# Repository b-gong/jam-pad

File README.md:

# jam-pad
Just Another Macro Pad

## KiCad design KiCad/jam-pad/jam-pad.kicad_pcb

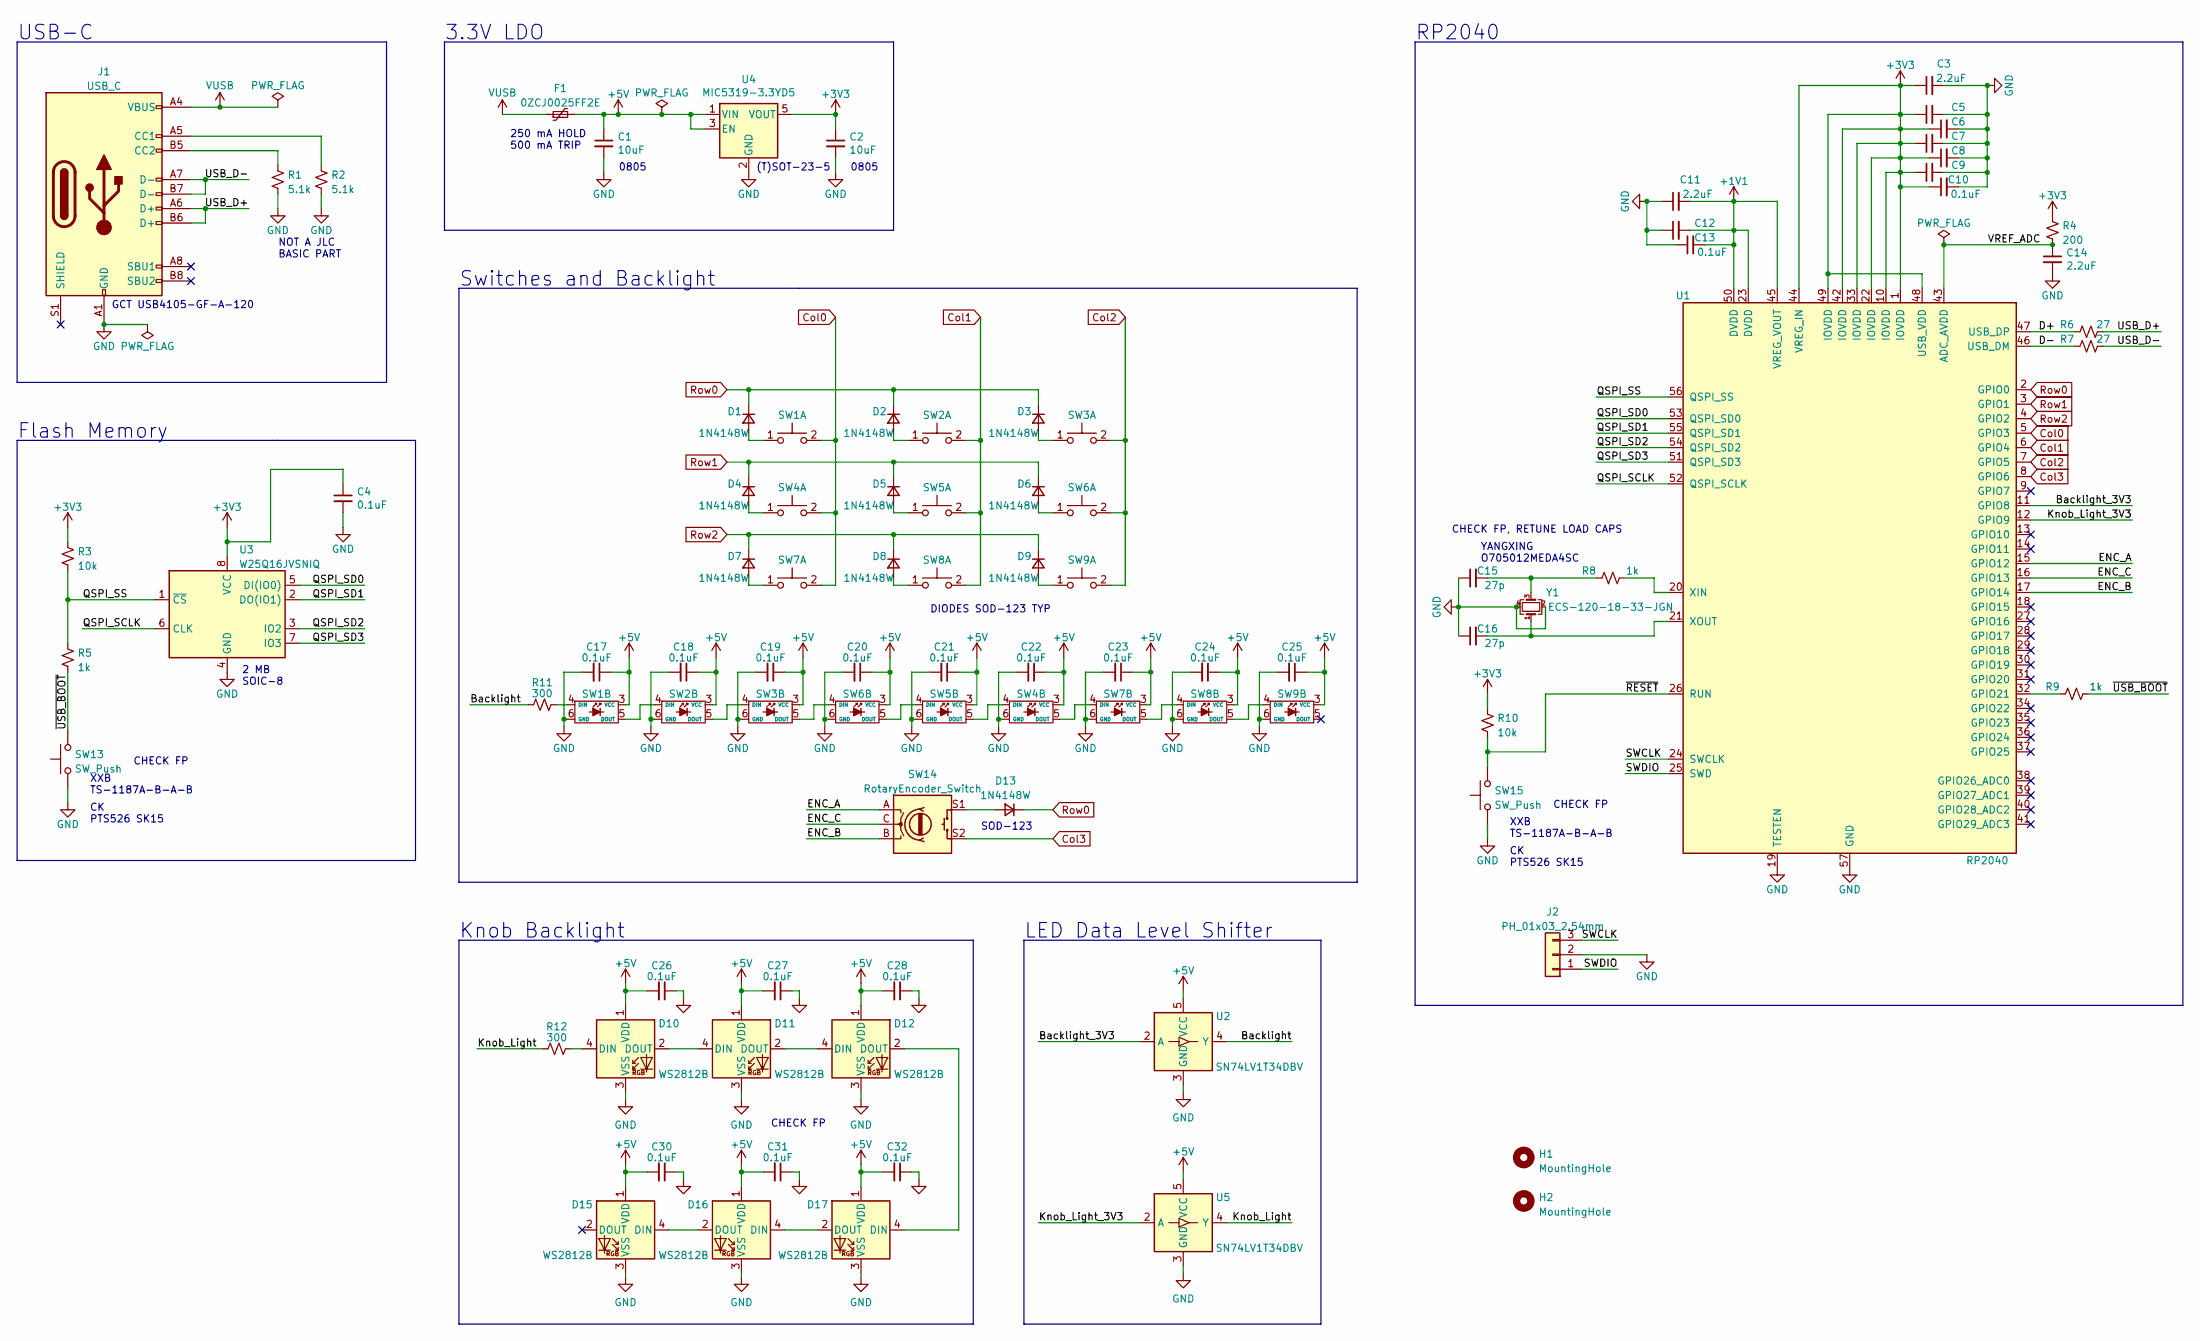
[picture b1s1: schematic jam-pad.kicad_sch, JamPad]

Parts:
C1, C2: 10uF; C_0805_2012Metric_Pad1.18x1.45mm_HandSolder; LCSC C19702
C3, C11, C14: 2.2uF; C_0603_1608Metric_Pad1.08x0.95mm_HandSolder; LCSC C23630
C4, C5, C6, C7, C8, C9, C10, C12, C13, C17, C18, C19, C20, C21, C22, C23, C24, C25, C26, C27, C28, C30, C31, C32: 0.1uF; C_0603_1608Metric_Pad1.08x0.95mm_HandSolder; LCSC C107045
C15, C16: 27p; C_0603_1608Metric_Pad1.08x0.95mm_HandSolder; LCSC C14663
D1, D2, D3, D4, D5, D6, D7, D8, D9, D13: 1N4148W; D_SOD-123; LCSC C81598
D10, D11, D12, D15, D16, D17: WS2812B; LED_WS2812B_PLCC4_5.0x5.0mm_P3.2mm; LCSC C2761795
F1: 0ZCJ0025FF2E; Fuse_1206_3216Metric_Pad1.42x1.75mm_HandSolder; JLCPCB_IGNORE Y
H1, H2: MountingHole; MountingHole_2.2mm_M2_Pad; JLCPCB_IGNORE Y
J1: USB_C; USB_C_Receptacle_GCT_USB4105-GF-A-120; JLCPCB_IGNORE Y
J2: PH_01x03_2.54mm; PinHeader_1x03_P2.54mm_NoSilk; JLCPCB_IGNORE Y
R1, R2: 5.1k; R_0603_1608Metric_Pad0.98x0.95mm_HandSolder; JLCPCB_IGNORE Y
R3, R10: 10k; R_0603_1608Metric_Pad0.98x0.95mm_HandSolder; LCSC C25804
R4: 200; R_0603_1608Metric_Pad0.98x0.95mm_HandSolder; LCSC C8218
R5, R8, R9: 1k; R_0603_1608Metric_Pad0.98x0.95mm_HandSolder; LCSC C21190
R6, R7: 27; R_0603_1608Metric_Pad0.98x0.95mm_HandSolder; LCSC C25190
R11, R12: 300; R_0603_1608Metric_Pad0.98x0.95mm_HandSolder; LCSC C23025
SW1, SW2, SW3, SW7, SW8, SW9: MX_Hotswap_LED_RGB; MXOnly-1U-Hotswap-SK6812MINI-E_180; JLCPCB_IGNORE Y
SW4, SW5, SW6: MX_Hotswap_LED_RGB; MXOnly-1U-Hotswap-SK6812MINI-E; JLCPCB_IGNORE Y
SW13, SW15: SW_Push; SW_Push_PTS526; LCSC C318884
SW14: RotaryEncoder_Switch; PEC11; JLCPCB_IGNORE Y
U1: RP2040; RP2040-QFN-56; LCSC C2040
U2, U5: SN74LV1T34DBV; SOT-23-5; LCSC C100024
U3: W25Q16JVSNIQ; SOIC-8_3.9x4.9mm_P1.27mm; LCSC C2456211
U4: MIC5319-3.3YD5; SOT-23-5; JLCPCB_IGNORE Y
Y1: ECS-120-18-33-JGN; Crystal_SMD_SeikoEpson_FA238-4Pin_3.2x2.5mm; LCSC C15918

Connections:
+1V1: C11.2, C12.2, C13.2, U1.23 (DVDD), U1.45 (VREG_VOUT), U1.50 (DVDD)
+3V3: C2.1, C3.1, C4.1, C5.1, C6.1, C7.1, C8.1, C9.1, C10.1, R3.1, R4.1, R10.1, U1.1 (IOVDD), U1.10 (IOVDD), U1.22 (IOVDD), U1.33 (IOVDD), U1.42 (IOVDD), U1.44 (VREG_IN), U1.48 (USB_VDD), U1.49 (IOVDD), U3.8 (VCC), U4.5 (VOUT)
+5V: C1.1, C17.1, C18.1, C19.1, C20.1, C21.1, C22.1, C23.1, C24.1, C25.1, C26.2, C27.2, C28.2, C30.2, C31.2, C32.2, D10.1 (VDD), D11.1 (VDD), D12.1 (VDD), D15.1 (VDD), D16.1 (VDD), D17.1 (VDD), F1.2, SW1.3 (VCC), SW2.3 (VCC), SW3.3 (VCC), SW4.3 (VCC), SW5.3 (VCC), SW6.3 (VCC), SW7.3 (VCC), SW8.3 (VCC), SW9.3 (VCC), U2.5 (VCC), U4.1 (VIN), U4.3 (EN), U5.5 (VCC)
/Backlight: R11.1, U2.4 (Y)
/Backlight_3V3: U1.11 (GPIO8), U2.2 (A)
/D+: R6.1, U1.47 (USB_DP)
/D-: R7.1, U1.46 (USB_DM)
/ENC_A: SW14.A, U1.15 (GPIO12)
/ENC_B: SW14.B, U1.17 (GPIO14)
/ENC_C: SW14.C, U1.16 (GPIO13)
/Knob_Light: R12.1, U5.4 (Y)
/Knob_Light_3V3: U1.12 (GPIO9), U5.2 (A)
/QSPI_SCLK: U1.52 (QSPI_SCLK), U3.6 (CLK)
/QSPI_SD0: U1.53 (QSPI_SD0), U3.5 (DI(IO0))
/QSPI_SD1: U1.55 (QSPI_SD1), U3.2 (DO(IO1))
/QSPI_SD2: U1.54 (QSPI_SD2), U3.3 (IO2)
/QSPI_SD3: U1.51 (QSPI_SD3), U3.7 (IO3)
/QSPI_SS: R3.2, R5.1, U1.56 (QSPI_SS), U3.1 (~CS)
/SWCLK: J2.3, U1.24 (SWCLK)
/SWDIO: J2.1, U1.25 (SWD)
/USB_D+: J1.A6 (D+), J1.B6 (D+), R6.2
/USB_D-: J1.A7 (D-), J1.B7 (D-), R7.2
/VREF_ADC: C14.1, R4.2, U1.43 (ADC_AVDD)
/~RESET: R10.2, SW15.2, U1.26 (RUN)
/~USB_BOOT: R5.2, R9.2, SW13.2
Col0: SW1.2, SW4.2, SW7.2, U1.5 (GPIO3)
Col1: SW2.2, SW5.2, SW8.2, U1.6 (GPIO4)
Col2: SW3.2, SW6.2, SW9.2, U1.7 (GPIO5)
Col3: SW14.S2, U1.8 (GPIO6)
GND: C1.2, C2.2, C3.2, C4.2, C5.2, C6.2, C7.2, C8.2, C9.2, C10.2, C11.1, C12.1, C13.1, C14.2, C15.1, C16.1, C17.2, C18.2, C19.2, C20.2, C21.2, C22.2, C23.2, C24.2, C25.2, C26.1, C27.1, C28.1, C30.1, C31.1, C32.1, D10.3 (VSS), D11.3 (VSS), D12.3 (VSS), D15.3 (VSS), D16.3 (VSS), D17.3 (VSS), J1.A1 (GND), J1.A12 (GND), J1.B1 (GND), J1.B12 (GND), J2.2, R1.2, R2.2, SW1.6 (GND), SW2.6 (GND), SW3.6 (GND), SW4.6 (GND), SW5.6 (GND), SW6.6 (GND), SW7.6 (GND), SW8.6 (GND), SW9.6 (GND), SW13.1, SW15.1, U1.19 (TESTEN), U1.57 (GND), U2.3 (GND), U3.4 (GND), U4.2 (GND), U5.3 (GND), Y1.2, Y1.4
unnamed: C15.2, R8.1, Y1.3
unnamed: D1.2 (A), SW1.1
unnamed: D2.2 (A), SW2.1
unnamed: D3.2 (A), SW3.1
unnamed: D4.2 (A), SW4.1
unnamed: D5.2 (A), SW5.1
unnamed: D6.2 (A), SW6.1
unnamed: D7.2 (A), SW7.1
unnamed: D8.2 (A), SW8.1
unnamed: D9.2 (A), SW9.1
unnamed: D10.4 (DIN), R12.2
unnamed: D10.2 (DOUT), D11.4 (DIN)
unnamed: D11.2 (DOUT), D12.4 (DIN)
unnamed: D12.2 (DOUT), D17.4 (DIN)
unnamed: D13.2 (A), SW14.S1
unnamed: D15.4 (DIN), D16.2 (DOUT)
unnamed: D16.4 (DIN), D17.2 (DOUT)
unnamed: J1.A5 (CC1), R2.1
unnamed: J1.B5 (CC2), R1.1
unnamed: R11.2, SW1.4 (DIN)
unnamed: SW1.5 (DOUT), SW2.4 (DIN)
unnamed: SW2.5 (DOUT), SW3.4 (DIN)
unnamed: SW3.5 (DOUT), SW6.4 (DIN)
unnamed: SW4.4 (DIN), SW5.5 (DOUT)
unnamed: SW4.5 (DOUT), SW7.4 (DIN)
unnamed: SW5.4 (DIN), SW6.5 (DOUT)
unnamed: SW7.5 (DOUT), SW8.4 (DIN)
unnamed: SW8.5 (DOUT), SW9.4 (DIN)
unnamed: R9.1, U1.32 (GPIO21)
unnamed: R8.2, U1.20 (XIN)
unnamed: C16.2, U1.21 (XOUT), Y1.1
Row0: D1.1 (K), D2.1 (K), D3.1 (K), D13.1 (K), U1.2 (GPIO0)
Row1: D4.1 (K), D5.1 (K), D6.1 (K), U1.3 (GPIO1)
Row2: D7.1 (K), D8.1 (K), D9.1 (K), U1.4 (GPIO2)
VUSB: F1.1, J1.A4 (VBUS), J1.A9 (VBUS), J1.B4 (VBUS), J1.B9 (VBUS)

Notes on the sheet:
2 MB SOIC-8
(T)SOT-23-5
CK PTS526 SK15
GCT USB4105-GF-A-120
DIODES SOD-123 TYP
250 mA HOLD 500 mA TRIP
Knob Backlight
NOT A JLC BASIC PART
CHECK FP
Switches and Backlight
USB-C
Flash Memory
XXB TS-1187A-B-A-B
3.3V LDO
LED Data Level Shifter
YANGXING O705012MEDA4SC
0805
RP2040
CHECK FP, RETUNE LOAD CAPS
SOD-123

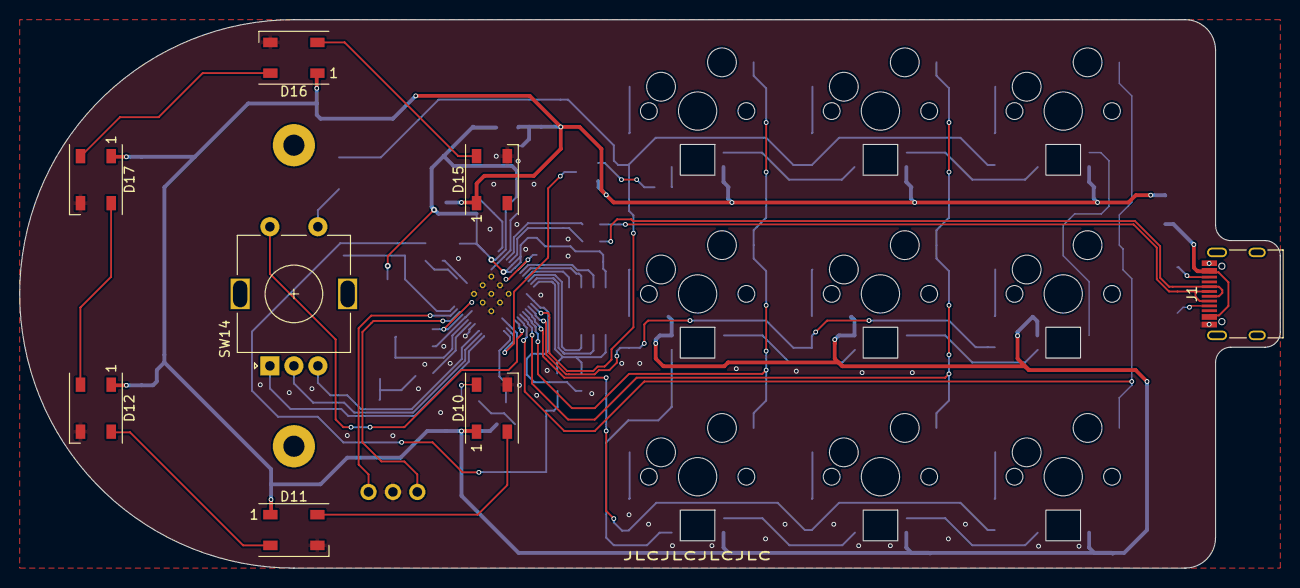
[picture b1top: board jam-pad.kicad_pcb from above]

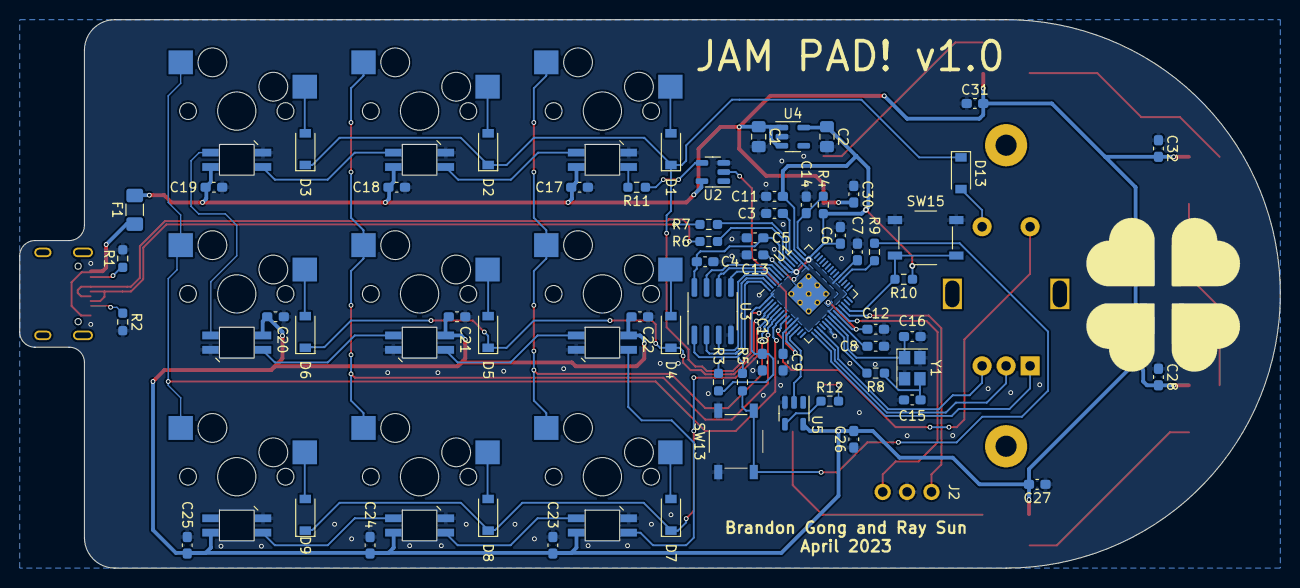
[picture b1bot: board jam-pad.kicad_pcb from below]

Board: 2 copper layers, 131.3 x 57.1 mm, 83 parts (64 on the bottom side), 65 nets.

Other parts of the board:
Ref**: Val**; cloverlogo

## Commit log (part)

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2022-10-30 created project, added basic stuff + jackrabbit rp2040
2022-12-26 update gitignore, some unknown schematic changes
2022-12-26 Assign footprints
2022-12-27 mx_only fp lib and replace switch footprints
2022-12-27 symbol attempt
2022-12-27 Make multi-unit fooprint for MX key with RGB LED
2022-12-27 Clean up symbol dependencies and pass ERC with schematic so far
2023-01-14 added jlc part datasheets (cap, res, 1n4148, rp2040)
2023-01-17 initial layout
2023-01-17 moved d13 to bottom
2023-02-01 12 to 9 keys
2023-02-01 Place MCU parts
2023-02-02 add reverse mounted sk6812/ws2812 fp
2023-02-09 hotswap sk6812 fp, did i forgot to add before
2023-03-17 added multi part sym for switch+led, remove backups
2023-03-17 Add JLCPCB design rules and preliminary route MCU
2023-03-29 changed underglow to knoblight, added led c and r, placed leds
2023-03-29 knob leds moved to top
2023-04-01 initial routing
2023-04-03 idk how to route + forgot to put flipped led switch fp in
2023-04-21 mcu placing + routing, power LED on 5V and level shifter
2023-04-22 Add symbol fields for KiKit
2023-04-22 Make KiKit makefile
2023-04-22 bit of power routing
2023-04-22 finished everything besides ground preliminarily
2023-04-23 initial plate stuff
2023-04-26 routing adjustments, ec11 standoff, need to fix drc kms
2023-04-27 some more routing adjustments, move plate to its own folder. should be done besides footprint drc errors, deco, maybe replace rp2040 fp
2023-04-27 Ignore DRC in KiKit makefile
2023-04-27 Remove unconnected tracks and pass schematic parity
2023-04-27 fix up usb_boot; bare minimum gnd vias; fix silkscreen overlap
2023-05-07 Add simple key matrix test code, USB printf
2023-05-10 fab, clover logo, some other stuff? idr sorry
2023-09-24 outdated case, updated pec11
2023-09-24 case
2023-09-29 renmae ver1 files
2023-09-29 some ver2 fixes, not done yet
2023-10-11 v2 models
